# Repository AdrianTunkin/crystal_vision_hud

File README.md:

# CRYSTAL VISION HUD
### Head-Up Display (HUD) System for safe driving

#### Attention: This repository does not contain diagrams and drawings of projector optics. 
#### Also repository does not contain information regarding mechanical parts, including servos.

Crystal Vision is a portable Head-Up Display (HUD) system that projects an image on the windshield of your car. 
Both the driver and the passengers see it as a semi-transparent image that “levitates” over the hood of the car.

#### Copyright (C) 2015-2018, Crystal Vision Ltd.

https://user-images.githubusercontent.com/49099551/141296656-99a9382b-fc6b-408f-bb68-5c6743e9c2cb.mp4

## VISUAL CHARACTERISTICS

* Resolution: 854 x 480
* Perceived distance: 1.8-2.2 meters (depends on winshield geometry)
* Size: 17"
* Frequency: 60 Hz
* Color coverage:  ~70% sRGB
* Brightness: 1150 cd/m² (only for visible parts)
* Proprietary Remote Canvas technology

## TECHNICAL SPECIFICATIONS

* CPU: Allwinner H6 Quad-Core 64-bit Cortex-A53 @ 1.8GHz
* RAM: LPDDR3 2Gb @ 533Mhz
* ROM: 32Gb TF/MMC
* Power supply: DC 12V, 1.2A (max)
* Interfaces: IEEE 802.11 b/g/n (WiFi), Bluetooth 5.1, USB 2.0, OBDII
* Control OS: Android 9.0 Pie
* Dimensions: 83mm x 52mm x 30mm
* Weight: 115g

## TERMINOLOGY

* Projector - device for displaying projected images in windshield.
* Host phone — the phone on which the manager and client applications are installed.
* Manager - a gateway program through which client applications send graphic messages to the projector.
* Client application - an android application that, using the RemoteCanvas API, draws graphic messages on the projector. 

## DESCRIPTION

The CRYSTAL_HUD_MANAGER module is an android application that is installed on the host phone and acts as a gateway through which applications send messages to the projector.

The CRYSTAL_HUD_MANAGER function as a gateway includes:
* Controlling the concurrent access model of client applications to the projector
* Prioritize access for different applications
* Authorization of client applications.
* Work with three modes: asynchronous messages, synchronous messages, streaming. 

## WEB RESOURCES:

http://crystal-hud.tech Crystal Vision HUD information web site

https://github.com/AdrianTunkin/crystal_vision_hud - GitHub web site hosting the Hardware and Software sources

## LICENSE

### HARDWARE
The Hardware project is released under the Creative Commons Attribution-Share Alike 3.0 United States License.
You may reproduce it for both your own personal use, and for commercial use. 
You will have to provide a link to the original creator of the project http://crystal-hud.tech on any documentation or website.
You may also modify the files, but you must then release them as well under the same terms.
Credit can be attributed through a link to the creator website: http://crystal-hud.tech

### SOFTWARE
The software is released under GPL3.

### DOCUMENTATION
The documentation is released under the Creative Commons Attribution-Share Alike 3.0 United States License.

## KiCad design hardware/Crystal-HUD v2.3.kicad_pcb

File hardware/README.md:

# CRYSTAL VISION HUD
### Head-Up Display (HUD) System for safe driving

Crystal Vision is a portable Head-Up Display (HUD) system that projects an image on the windshield of your car. 
Both the driver and the passengers see it as a semi-transparent image that “levitates” over the hood of the car.

#### Copyright (C) 2015-2018, Crystal Vision Ltd.

Hardware directory contains hardware schematics, design sources, and revision changes designed in KiCad EDA software.

The Crystal Vision HUD electronic board is 6 layer PCB.

#### Technical specifications

* CPU: Allwinner H6 Quad-Core 64-bit Cortex-A53 @ 1.8GHz
* RAM: LPDDR3 2Gb @ 533Mhz
* ROM: 32Gb TF/MMC
* Power supply: DC 12V, 1.2A (max)
* Interfaces: IEEE 802.11 b/g/n (WiFi), Bluetooth 5.1, USB 2.0

### Hardware revision changes log:

#### Hardware revision 1.0

* initial release

#### Hardware revision 1.1

* 1. Adjusted white print of label
* 2. Added bypass near FET2
* 3. Added white print for the UART connector at the bottom of the board
* 4. Fixed white print of R106 and R116
* 5. R29 placed a bit further from C84

#### Hardware revision 2.0

* 1. Changed from eMMC 4GB 1.00mm pitch to eMMC  16GB 0.50mm pitch.
* 2. C212 and C213 were increased to 33pF and to 0402.
* 3. R66 value changed from NA(0R) to NA(22R)
* 4. RM15's package changed from RA1206_(4X0603)_4B8_22R to RA0805_(4X0402)_22R as component optimisation.
* 5. C119 and VR1 changed from PTH to SMT type in the KiCad settings. In reallity, C119 and VR1 did not change. 
* 6. PWRLED1 and CHGLED1 labels corrected in the white print.
* 7. WP_Enable1 jumper added to the SPI_Flash.
* 8. U4 changed from NA(H27UBG8T2BTR-BC(TSOP48)) to NA(MT29F64G08CBABA-WP(TSOP48)), i.e. when populated 8GB NAND instead of 4GB.

#### Hardware revision 2.1

* 1. eMMC KLMAG2GEND-B031(FBGA153)(16G) changed with new eMMC KLMAG1JETD-B041(FBGA153)(16G)

#### Hardware revision 2.2

* 1. Added R62(10k/0402) pull-down to the eMMC's data strobe line;
* 2. RM14, RA0805_(4X0402)_22R replaced by 4 resistors 22R/0402, i.e. R121-R124;
* 3. R73[NA(22R/0402)] was added to enable SPI0 software CS option to the UEXT via PH10, when the SPI_Flash is populated.
* 4. L9 was changed from 2.7nH/L0402 to NA(2.7nH/L0402), and C88 from 24pF to NA(24pF);
* 5. MIPI-DSI1 changed: MIPI-DSI1 connector's pinout completely changed for Raspberry-Pi compatability; added the resistors: R125 to R132;
* 6. In the DRC drill to drill clerance was set to 12mils and all related errors were corrected;
* 7. UEXT1 was changed from NA(HN2x5) to HN2x5;
* 8. All 3Ds were assigned;
* 9. It was added C94(NA/0402) to the eMMC's clock line just in case;
* 10. NAND and related components removed forever;
* 11. In the schematic all "/" signs were exchanged with "\";
* 12. Improvements around the placement of a number of resistors related to the PHY signals to reduce EMI emissions;
* 13. Added U4 EEPROM - AT24C16C-SSHM-T(SOIC-8_150mil) and also C39, 100nF/10V/10% to the UEXT's I2C to avoid conflict with the same EEPROM
* 14. R15[NA(22R/R0402)] added in serial to the eMMC's datastrobe signal to be able to disconnect when no HS400 mode or to add a serial filter to reduce EMI;
* 15. U2 and U3's packages improved;

#### Hardware revision 2.3

* 1. Added antenna ANT2(NA(U.FL-R-SMT-1)), R16(0R) and R17(NA/0R);
* 2. Removed FB1(FB0402/PZ1005U601-R45TF-1) and FB2(FB0402/PZ1005U601-R45TF-1) and placed R18(22R/0402) and R19(22R/0402) resistors instead.;
* 3. Adjusted the lengths of some eMMC wires;
* 4. C93 changed from 24pF to 24pF\50V/5%. C88 and C198 changed from NA/24pF to NA(24pF\50V/5%);
* 5. Changing 5.1 eMMC at 3.3V (up from 1.8V operation) for better reliability, PWR_PC1 jumper has to be set to position 1-2 for 3.3V operation.

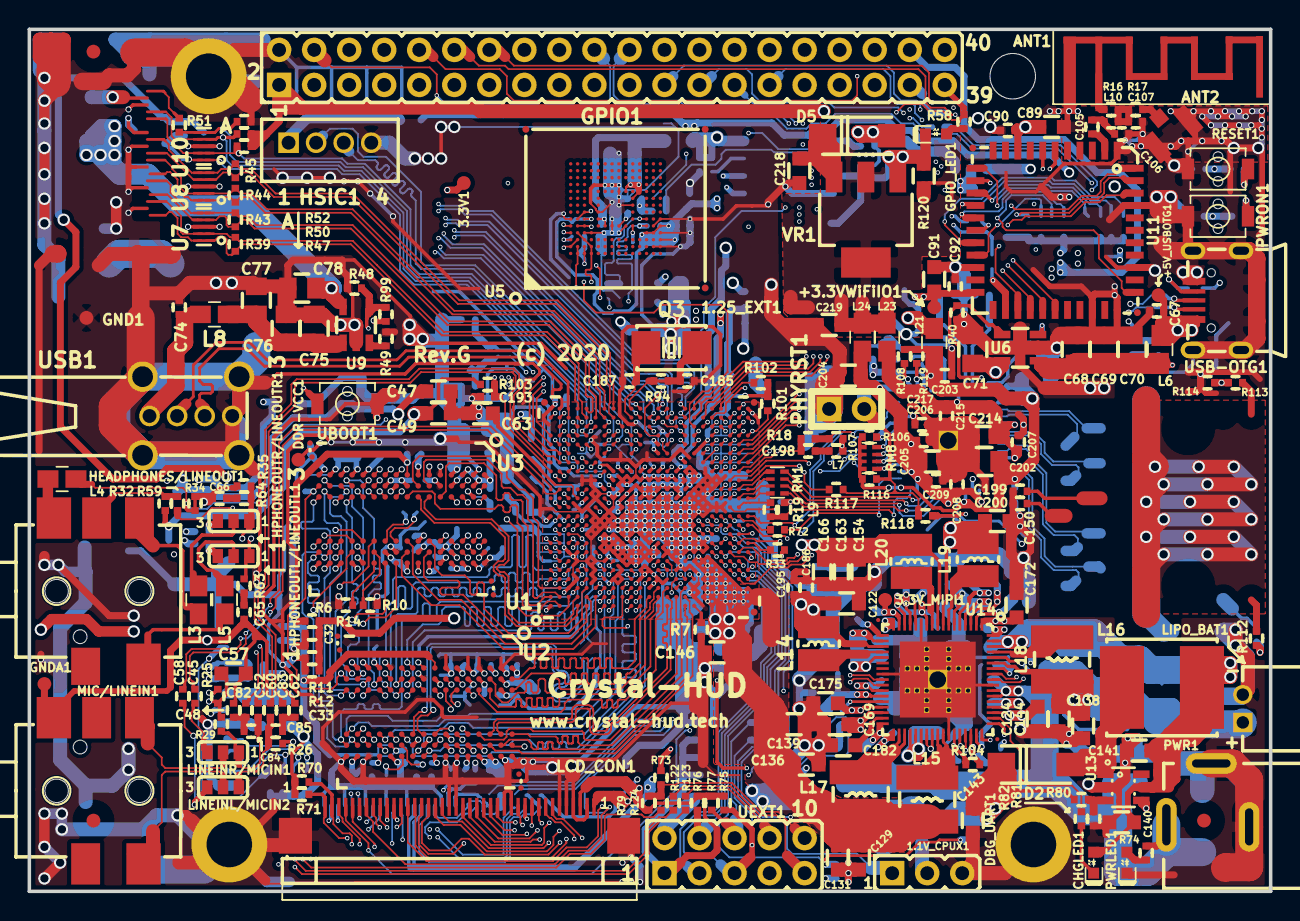
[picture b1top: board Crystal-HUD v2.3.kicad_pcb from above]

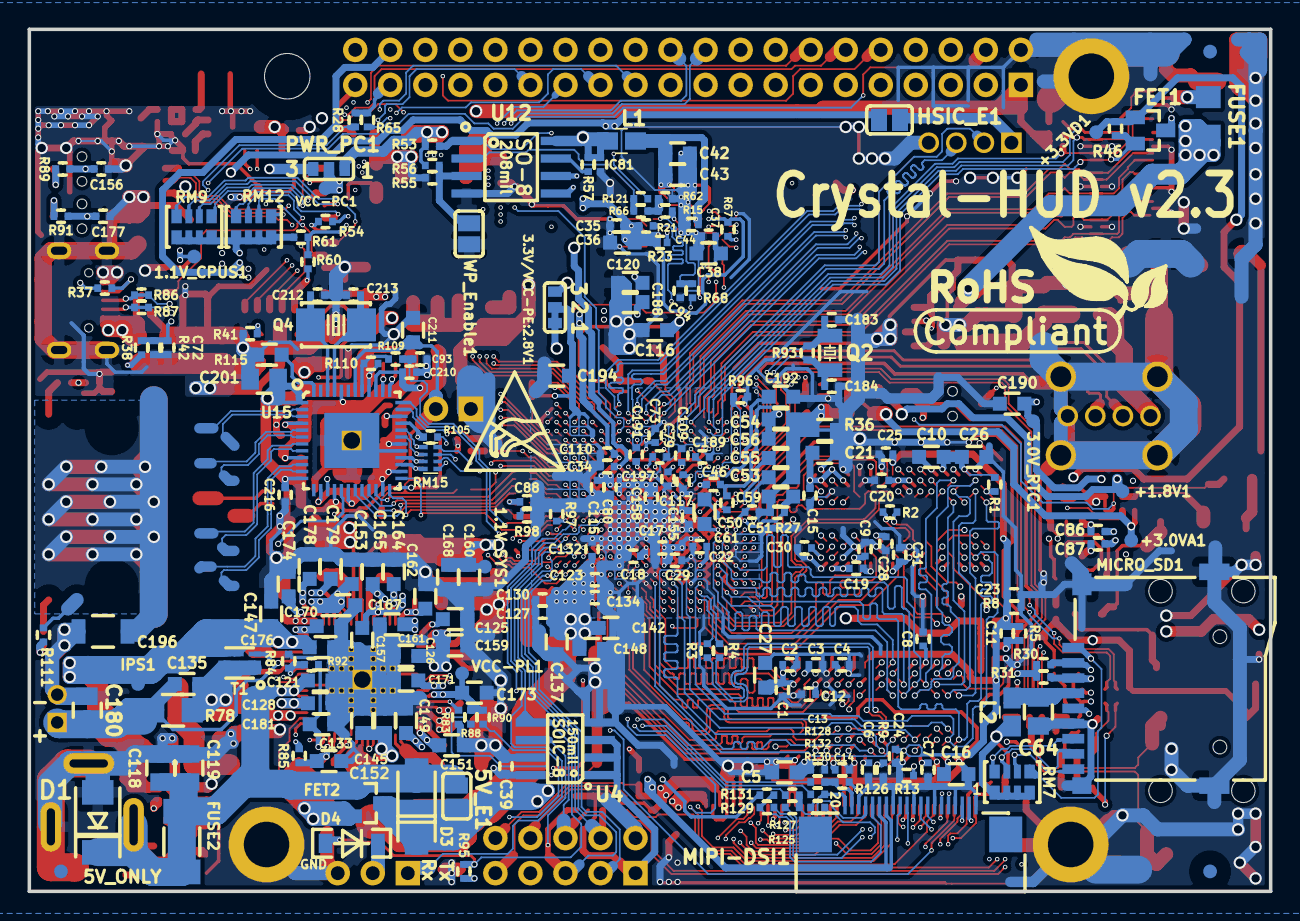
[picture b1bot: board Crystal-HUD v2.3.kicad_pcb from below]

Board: 6 copper layers, 90.0 x 62.5 mm, 445 parts (229 on the bottom side), 396 nets.

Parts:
1.1V_CPUS1, 1.1V_CPUX1, 1.1V_SYS1, 1.25_EXT1, 3.0V_RTC1, 3.3V1, 3.3V_MIPI1: TESTPAD; TP_SMD
3.3V/VCC-PE:2.8V1: Opened(2-3);Closed(1-2); SJ_2_SMALL_12_TIED
5V_E1: Opened; SJ
+1.8V1, +3.0VA1, +3.3VD1, +3.3VWiFiIO1, +5V_USBOTG1: TESTPAD; TP_SMD
ANT1: PCB_WIFI_ANT; BT_Antenna_Inverted_1ANT_2GND
ANT2: NA(U.FL-R-SMT-1); U.FL-R-SMT-1
C1, C2, C3, C4, C6, C7, C8, C9, C11, C12, C13, C14, C15, C17, C18, C19, C20, C22, C23, C24, C25, C32, C33, C34, C45, C46, C50, C51, C52, C58, C60, C65, C66, C67, C72, C73, C74, C79, C80, C82, C83, C86, C87, C109, C110, C115, C117, C123, C127, C130, C132, C134, C155, C156, C158, C177, C186, C189, C191, C195, C197, C199, C200, C203, C206, C207, C208, C209, C210, C215, C216, C217: 100nF\10V/10%; C_0402_5MIL_DWS
C5, C10, C16, C21, C47, C49, C53, C54, C57, C59, C63, C116, C121, C122, C124, C125, C126, C128, C129, C131, C133, C136, C138, C139, C140, C141, C143, C144, C145, C146, C147, C148, C149, C150, C151, C152, C153, C154, C157, C159, C161, C162, C164, C165, C166, C167, C168, C169, C170, C171, C172, C173, C175, C176, C178, C179, C188, C192, C194: 10uF\6.3V/20%; C_0603_5MIL_DWS
C26: 10uF/6.3V/20%; C_0603_5MIL_DWS
C27: 1uF/10V/10%; C_0603_5MIL_DWS
C28, C29, C30, C31, C39: 100nF/10V/10%; C_0402_5MIL_DWS
C35, C37, C44, C81, C90, C92: NA(100nF\10V/10%); C_0402_5MIL_DWS
C36, C38, C43: NA(2.2uF\6.3V/10%); C_0603_5MIL_DWS
C42: NA(22uF\6.3V/20%); C_0603_5MIL_DWS
C48, C62, C84, C85, C185, C187, C212, C213: 33pF\50V/5%; C_0402_5MIL_DWS
C55, C120, C135, C137, C142, C160, C163, C181, C182, C190, C211: 1uF\10V/10%; C_0603_5MIL_DWS
C56, C61: 2.2uF\6.3V/10%; C_0603_5MIL_DWS
C64, C68, C71, C75, C78, C118, C119, C180, C201, C202: 47uF\6.3V/20%; C_0805_5MIL_DWS
C69, C70, C76, C77: NA(47uF\6.3V/20%); C_0805_5MIL_DWS
C88, C198: NA(24pF\50V/5%); C_0402_5MIL_DWS
C89, C91, C174: NA(10uF\6.3V/20%); C_0603_5MIL_DWS
C93: 24pF\50V/5%; C_0402_5MIL_DWS
C94: NA; C_0402_5MIL_DWS
C105: NA(10pF\50V/5%); C_0402_5MIL_DWS
C106: NA(0.8pF\C0402); C_0402_5MIL_DWS
C107: NA(1.5pF\C0402); C_0402_5MIL_DWS
C183, C184: 22pF\50V/5%; C_0402_5MIL_DWS
C193: NA(1nF\50V/10%); C_0402_5MIL_DWS
C196: 1nF\2kV/10%/X7R; C_1206_5MIL_DWS_ISO
C204, C205, C214, C218, C219: 22uF\6.3V/20%; C_0603_5MIL_DWS
CHGLED1: LED\YELLOW/0603; LED_0603_KA
D1: SMBJ6.0A; DO214AA_1(K)-2(A)
D2, D3: 1N5822\SS34/SMA; SMA-KA
D4: 1N5819(S4SOD-123); SOD-123_1C-2A_KA
D5: 1N4007\SMA; SMA-KA
DBG_UART1: HN1x3
DDR-VCC1: TESTPAD; TP_SMD
FET1: BSS138(SOT23-3); SOT23
FET2: IRLML6402(SOT-23); SOT23
FID1, FID2, FID3, FID4, FID5, FID6: Fiducial1x3_transp
FUSE1: FSMD035; FUSE-1206
FUSE2: NA(5025); FUSE-5025
GND1: TESTPAD; TP_SMD
GNDA1: TESTPAD; TESTPAD_40-ROUND
GPIO1: NA(HN2x20); HN2x20
GPIO_LED1: LED\Red/0603; LED_0603_KA
HEADPHONES/LINEOUT1: SCJ325P00XG0B02G
HPHONEOUTL/LINEOUTL1: Soldered(1-2);Opened(2-3); SJ_2_SMALL
HPHONEOUTR/LINEOUTR1: Soldered(1-2);Opened(2-3); SJ_2_SMALL
HSIC1: NA(B4B-PH-K-S); B4B-PH-K-S
HSIC_E1: Opened; SJ
IPS1: TESTPAD; TP_SMD
L1: NA(FB0805\600R/2A); L_0805_5MIL_DWS
L2, L3, L4, L5, L6, L8, L21, L23, L24: FB0805\600R/2A; L_0805_5MIL_DWS
L7, L9: NA(2.7nH\L0402); L_0402_5MIL_DWS
L10: NA(3.3nH +-0.1nH LQP15MN3N3B02D); L_0402_5MIL_DWS
L14, L19, L20: SWPA3015S1R5NT(1.5uH\2.30A/DCR<0.1R/CD32); CD32
L15, L17, L18: SWPA4018S1R5NT(1.5uH\3.35A/DCR<0.1R/CD43); CD42(43)
L16: 2.2uH\3A/YS75/7x8; YS75_7X8MM
LCD_CON1: FPV-WZA21-40-LF
LINEINL/MICIN2: Opened(2-3);Soldered(1-2); SJ_2_SMALL
LINEINR/MICIN1: Opened(2-3);Soldered(1-2); SJ_2_SMALL
LIPO_BAT1: DW02R; LIPO_BAT-CON2DW02R
MIC/LINEIN1: SCJ325P00XG0B02G
MICRO_SD1: MICRO_SD(TFC-WPAPR-08); TFC-WPAPR-08
MIPI-DSI1: FPV-WZA21-20-LF
Mounting_hole1, Mounting_hole2, Mounting_hole3: Mounting_hole; Mounting_hole_3.3mm_with_5.5mm_pad
Mounting_hole4: Mounting_hole; Mounting_hole_3.3mm
PHYRST1: HN1x2(Opened); HN1x2_Jumper
PWR1: PWRJ-2mm(YDJ-1134)
PWRLED1: LED\Red/0603; LED_0603_KA
PWRON1: IT-1185AU2-160G-G-TR; IT1185AU2_V2
PWR_PC1: Opened(2-3);Soldered(1-2); SJ_2_SMALL
Q2: Q32.768kHz/12.5pF/2P/SMD1206; CM7V-T1A(Crystal_Package-1206_3.20x1.50x0.65mm)
Q3: Q24MHZ\20pF/20ppm/2P/5x3.2mm; HCX-4S_2Pins_5.0x3.2mm_TEST
Q4: Q25MHz\20pF/20ppm/2P/5x3.2mm; HCX-4S_2Pins_5.0x3.2mm_TEST
R1, R5, R8, R11, R12, R26, R29: 2k\1%; R_0402_5MIL_DWS
R2: 100R\1%; R_0402_5MIL_DWS
R3, R4, R18, R19, R33, R63, R64, R65, R72, R105, R109, R121, R122, R123, R124, R125, R126, R129, R130: 22R; R_0402_5MIL_DWS
R6, R55, R84, R96, R97, R98, R118, R127, R128, R131, R132: NA; R_0402_5MIL_DWS
R7, R9, R10: 243R\1%; R_0402_5MIL_DWS
R13, R14: NA(243R\1%); R_0402_5MIL_DWS
R15, R54, R66, R68, R73: NA(22R); R_0402_5MIL_DWS
R16: 0R; R_0402_5MIL_DWS
R17, R60: NA(0R); R_0402_5MIL_DWS
R21, R23, R48, R53, R56, R57, R61, R62, R67, R104: NA(10k); R_0402_5MIL_DWS
R25: 470R; R_0402_5MIL_DWS
R27: 200k\1%; R_0402_5MIL_DWS
R28: NA(1k); R_0402_5MIL_DWS
R30, R35, R103, R116: 100k; R_0402_5MIL_DWS
R31, R37, R40, R42, R52, R76, R79, R83, R85, R95, R99, R106, R119: 10k; R_0402_5MIL_DWS
R32: NA(1M); R_0402_5MIL_DWS
R34, R86, R87, R94: 0R(Board_Mounted); R_0402_5MIL_0R(Board_Mounted)
R36: 0R(Board_Mounted); R_0603_5MIL_0R(Board_Mounted)
R38, R51: 4.7k; R_0402_5MIL_DWS
R39, R43, R44, R45: NA(510R); R_0402_5MIL_DWS
R41: 13k\1%; R_0402_5MIL_DWS
R46: 27k; R_0402_5MIL_DWS
R47, R50, R70, R71, R74, R75, R77, R82, R88, R90: 2.2k; R_0402_5MIL_DWS
R49: 3.92k\1%; R_0402_5MIL_DWS
R58, R89, R91, R92, R107, R108, R110, R111, R112, R113, R114, R117: 1k; R_0402_5MIL_DWS
R59: 47k; R_0402_5MIL_DWS
R78: 0.01R\1%/1206; R_1206_5MIL_DWS
R80: 8.25k\1%; R_0402_5MIL_DWS
R81: 1.1k\1%; R_0402_5MIL_DWS
R93: 10M; R_0402_5MIL_DWS
R101, R102: NA(2.2k); R_0402_5MIL_DWS
R115: 12.1k\1%; R_0603_5MIL_DWS
R120: 120R; R_0603_5MIL_DWS
RESET1: IT-1185AU2-160G-G-TR; IT1185AU2_V2
RM1, RM15: RA0805_(4X0402)_22R; RA0805_(4X0402)_xx_BIGGEROUTPADS
RM7: RA1206_(4x0603)_4B8_100k; RA1206_(4X0603)_4B8_xx
RM8: RA0805_(4X0402)_4.7k; RA0805_(4X0402)_xx_BIGGEROUTPADS
RM9, RM12: NA(RA1206_(4x0603)_4B8_100k); RA1206_(4X0603)_4B8_xx
Sign-Antistatic: LOGO_ANTISTATIC_1
Sign-RoHS: LOGO_ROHS_1
T1: WPM1481-6\TR(DFN2X2-6L); DFN2x2-6L
U1: AllWinner-A64(FBGA396); FBGA396
U2, U3: K4B4G1646Q-HYK0(FBGA-96_256Mx16_DDR3-1600_11-11-1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; FBGA96(HYNIX_SAMSUNG_512MX16_DDR3)
U4: AT24C16C-SSHM-T(SOIC-8_150mil); SOIC-8_150mil
U5: NA(KLMAG2GEND-B031(FBGA153)); FBGA153_Pitch-0.5mm_Ball-0.25mm_Dimensions-11.50x13.00x0.80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
U6, U9: SY6280AAC(SOT23-5); SOT-23-5
U7, U8, U10: NA(RCLAMP0524P(SLP2510P8)); SLP2510P8_TEST
U11: NA(RTL8723BS(ComboModule)); RL-SM02BD(RTL8723BS)
U12: NA(W25Q128FVSIG); SO-8_208mil
U13: MT3608(SOT23-6); SOT23-6
U14: AXP803(QFN68_8x8mm); QFN68
U15: KSZ9031RNXCC(QFN48_1DRILL(PADPITCH-0.5MM)); QFN48_1DRILL(PADPITCH-0.5MM)
UBOOT1: IT-1185AU2-160G-G-TR; IT1185AU2_V2
UEXT1: HN2x5
USB1: USB_A_VERTICAL; USB_A_VERTICAL_PTH
USB-OTG1: MICRO_USB\MISB-SWMM-5B_LF; USB-MICRO_MISB-SWMM-5B_LF
VCC-PC1: TESTPAD; TP_SMD
VCC-PL1: TESTPAD; TP_SMD
VR1: AMS1117(ADJ); SOT223
WP_Enable1: Opened; SJ

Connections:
1.1V_CPUS: 1.1V_CPUS1.1, C117.2, C120.2, C179.2, U1.H15, U14.5
1.1V_CPUX: 1.1V_CPUX1.1, C123.2, C127.2, C129.2, C130.2, C131.2, C132.2, C134.2, C136.2, C137.2, C139.2, C142.2, C146.2, C148.2, L15.2, L17.2, U1.AA1, U1.AA3, U1.AB2, U1.AC1, U1.AC2, U1.U6, U1.V2, U1.V3, U1.V4, U1.V5, U1.V6, U1.W1, U1.W3, U1.W4, U1.W5, U1.Y2, U1.Y3, U1.Y4
1.1V_SYS: 1.1V_SYS1.1, C154.2, C155.2, C158.2, C160.2, C163.2, C166.2, C168.2, L20.2, U1.J12, U1.J13, U1.K14, U1.L13, U1.L14, U1.M13, U1.M14, U1.N14, U1.P14, U1.R13, U1.R14, U1.T15, U14.9
1.2V_HSIC: C178.2, C197.1, HSIC_E1.1, U1.K16, U14.3
3.0V_RTC: 3.0V_RTC1.1, C152.1, C189.2, C190.2, R85.2, R104.1, U1.H16, U14.49
+1.5V: C1.1, C2.1, C3.1, C4.1, C5.1, C6.1, C7.1, C8.1, C9.1, C10.1, C11.1, C12.1, C13.1, C14.1, C15.1, C16.1, C17.1, C18.1, C19.1, C20.1, C21.1, C26.1, C27.1, C28.1, C29.1, C30.1, C31.1, C32.2, C150.2, DDR-VCC1.1, L19.2, R1.2, R5.2, R11.2, U1.G7, U1.G8, U1.G9, U1.J8, U1.K6, U1.K7, U1.L6, U1.L7, U1.L8, U1.N7, U1.N8, U2.A1, U2.A8, U2.B2, U2.C1, U2.C9, U2.D2, U2.D9, U2.E9, U2.F1, U2.G7, U2.H2, U2.H9, U2.K2, U2.K8, U2.N1, U2.N9, U2.R1, U2.R9, U3.A1, U3.A8, U3.B2, U3.C1, U3.C9, U3.D2, U3.D9, U3.E9, U3.F1, U3.G7, U3.H2, U3.H9, U3.K2, U3.K8, U3.N1, U3.N9, U3.R1, U3.R9, U14.8
+1V8: +1.8V1.1, C47.2, C50.2, C170.2, PWR_PC1.3, U1.E13, U14.68
+3.0VA: +3.0VA1.1, C46.1, C49.1, C175.1, C191.2, R32.2, R103.1, U1.G14, U1.N16, U14.31
+3.3VD: +3.3VD1.1, C79.2, C161.2, FET1.1, R46.1, U1.M16, U14.17
+3.3VWiFiIO: +3.3VWiFiIO1.1, C91.2, C92.2, C110.2, C165.2, R61.2, RM9.1.1, RM9.2.1, RM9.3.1, RM9.4.1, RM12.1.1, RM12.2.1, RM12.3.1, RM12.4.1, U1.T17, U11.22, U14.13
+3V3: 3.3V1.1, 3.3V/VCC-PE:2.8V1.3, C39.1, C73.2, C80.1, C81.2, C89.2, C90.2, C115.2, C116.2, C122.2, C186.2, C195.2, D5.2, GPIO1.3, L1.1, L2.1, L14.2, L21.2, LCD_CON1.3, PWR_PC1.1, R30.2, R31.2, R37.2, R53.2, R56.2, R57.2, R70.2, R71.2, R75.1, R76.1, R77.1, R79.1, R95.2, R99.1, RM7.1.1, RM7.2.1, RM7.3.1, RM7.4.1, U1.L16, U1.N18, U1.N19, U1.T14, U1.U15, U1.U16, U4.1, U4.2, U4.3, U4.8, U11.9, U12.8, U13.4, U14.20, UEXT1.1
+5V: 5V_E1.2, C71.1, C78.1, D3.1, FET2.3, FUSE1.1, GPIO1.1, LCD_CON1.1, R47.1, R50.1, U6.5, U9.5
+5V_EXT: 5V_E1.1, C118.2, C119.2, C121.1, D1.1, D3.2, FET2.1, FUSE2.1, FUSE2.2, PWR1.+, R74.1, U14.57, U14.58
+5V_USBOTG: +5V_USBOTG1.1, C67.1, C124.1, L6.2, U14.54, USB-OTG1.1
/NAND Flash , eMMC, T-Card and Audio/HP-DET: R59.2, U1.D11
/NAND Flash , eMMC, T-Card and Audio/HPOUTFB: L4.1, R34.2, U1.C10
/NAND Flash , eMMC, T-Card and Audio/HPOUTL: HPHONEOUTL/LINEOUTL1.1, R63.2, U1.C13
/NAND Flash , eMMC, T-Card and Audio/HPOUTR: HPHONEOUTR/LINEOUTR1.1, R35.2, R64.2, U1.C12
/NAND Flash , eMMC, T-Card and Audio/LINEINL: C58.2, U1.B14
/NAND Flash , eMMC, T-Card and Audio/LINEINR: C45.2, U1.A14
/NAND Flash , eMMC, T-Card and Audio/LINEOUTL: C87.1, U1.D16
/NAND Flash , eMMC, T-Card and Audio/LINEOUTR: C86.1, U1.C16
/NAND Flash , eMMC, T-Card and Audio/MBIAS: R25.2, U1.E14
/NAND Flash , eMMC, T-Card and Audio/MICIN1N: C82.2, U1.B16
/NAND Flash , eMMC, T-Card and Audio/MICIN1P: C52.2, U1.B15
/NAND Flash , eMMC, T-Card and Audio/MICIN2N: C83.2, U1.A17
/NAND Flash , eMMC, T-Card and Audio/MICIN2P: C60.2, U1.B17
/NAND Flash , eMMC, T-Card and Audio/NAND0-ALE\SDC2-DS: R15.2, R62.1, R66.2, U1.K18
/NAND Flash , eMMC, T-Card and Audio/NAND0-DQ0\SDC2-D0: R67.1, U1.M21, U5.A3
/NAND Flash , eMMC, T-Card and Audio/NAND0-DQ1\SDC2-D1: U1.L19, U5.A4
/NAND Flash , eMMC, T-Card and Audio/NAND0-DQ2\SDC2-D2: U1.K20, U5.A5
/NAND Flash , eMMC, T-Card and Audio/NAND0-DQ3\SDC2-D3: U1.H20, U5.B2
/NAND Flash , eMMC, T-Card and Audio/NAND0-DQ4\SDC2-D4: U1.P18, U5.B3
/NAND Flash , eMMC, T-Card and Audio/NAND0-DQ5\SDC2-D5: U1.L20, U5.B4
/NAND Flash , eMMC, T-Card and Audio/NAND0-DQ6\SDC2-D6: U1.J21, U5.B5
/NAND Flash , eMMC, T-Card and Audio/NAND0-DQ7\SDC2-D7: U1.R21, U5.B6
/NAND Flash , eMMC, T-Card and Audio/NAND0-DQS\SDC2-RST: R23.1, U1.N20, U5.K5
/NAND Flash , eMMC, T-Card and Audio/NAND0-RB0\SDC2-CMD: R21.1, U1.K19, U5.M5
/NAND Flash , eMMC, T-Card and Audio/NAND0-RE\SDC2-CLK: R68.2, U1.G20
/NAND Flash , eMMC, T-Card and Audio/SDC0-CLK: R33.2, U1.AC8
/NAND Flash , eMMC, T-Card and Audio/SDC0-CMD: MICRO_SD1.3, R31.1, U1.W9
/NAND Flash , eMMC, T-Card and Audio/SDC0-D0: MICRO_SD1.7, RM7.1.2, U1.W13
/NAND Flash , eMMC, T-Card and Audio/SDC0-D1: MICRO_SD1.8, RM7.2.2, U1.AB10
/NAND Flash , eMMC, T-Card and Audio/SDC0-D2: MICRO_SD1.1, RM7.4.2, U1.AB9
/NAND Flash , eMMC, T-Card and Audio/SDC0-D3: MICRO_SD1.2, R30.1, U1.AB6
/NAND Flash , eMMC, T-Card and Audio/SDC0-DET#: MICRO_SD1.9, RM7.3.2, U1.AB8
/NAND Flash , eMMC, T-Card and Audio/eMMC_CLK: C94.1, R68.1, U5.M6
/Power Supply, Extensions and MiPi-DSI/1.8V_DVDD-CSI: C172.2, GPIO1.36, U14.1
/Power Supply, Extensions and MiPi-DSI/2.8V_AVDD-CSI: C164.2, GPIO1.38, U14.14
/Power Supply, Extensions and MiPi-DSI/3.3V_MIPI: 3.3V_MIPI1.1, C162.2, MIPI-DSI1.14, MIPI-DSI1.15, U14.16
/Power Supply, Extensions and MiPi-DSI/DC5SET: R84.2, R92.1, U14.62
/Power Supply, Extensions and MiPi-DSI/DSI-CKN: MIPI-DSI1.5, U1.P23
/Power Supply, Extensions and MiPi-DSI/DSI-CKP: MIPI-DSI1.6, U1.N23
/Power Supply, Extensions and MiPi-DSI/DSI-D0N: MIPI-DSI1.8, U1.T23
/Power Supply, Extensions and MiPi-DSI/DSI-D0P: MIPI-DSI1.9, U1.T22
/Power Supply, Extensions and MiPi-DSI/DSI-D1N: MIPI-DSI1.2, U1.R22
/Power Supply, Extensions and MiPi-DSI/DSI-D1P: MIPI-DSI1.3, U1.P22
/Power Supply, Extensions and MiPi-DSI/DSI-D2N: R126.2, U1.N22
/Power Supply, Extensions and MiPi-DSI/DSI-D2P: R130.1, U1.M22
/Power Supply, Extensions and MiPi-DSI/DSI-D3N: R129.1, U1.L22
/Power Supply, Extensions and MiPi-DSI/DSI-D3P: R125.2, U1.L23
/Power Supply, Extensions and MiPi-DSI/MIPI-DSI-BKL: R132.1, U1.W8
/Power Supply, Extensions and MiPi-DSI/MIPI-DSI-EN: R128.2, U1.Y6
/Power Supply, Extensions and MiPi-DSI/MIPI-DSI-RST: R127.2, U1.AA6
/Power Supply, Extensions and MiPi-DSI/PB0: GPIO1.10, U1.V9
/Power Supply, Extensions and MiPi-DSI/PB1: GPIO1.12, U1.AB7
/Power Supply, Extensions and MiPi-DSI/PB2: GPIO1.14, U1.W10
/Power Supply, Extensions and MiPi-DSI/PB3: GPIO1.16, U1.AA7
/Power Supply, Extensions and MiPi-DSI/PB4: GPIO1.18, U1.W7
/Power Supply, Extensions and MiPi-DSI/PE0: GPIO1.5, U1.AA18
/Power Supply, Extensions and MiPi-DSI/PE1: GPIO1.7, U1.AB23
/Power Supply, Extensions and MiPi-DSI/PE2: GPIO1.9, U1.AA22
/Power Supply, Extensions and MiPi-DSI/PE3: GPIO1.11, U1.AA21
/Power Supply, Extensions and MiPi-DSI/PE4: GPIO1.13, U1.AA19
/Power Supply, Extensions and MiPi-DSI/PE5: GPIO1.15, U1.W17
/Power Supply, Extensions and MiPi-DSI/PE6: GPIO1.17, U1.W20
/Power Supply, Extensions and MiPi-DSI/PE7: GPIO1.19, U1.Y19
/Power Supply, Extensions and MiPi-DSI/PE8: GPIO1.21, U1.AC22
/Power Supply, Extensions and MiPi-DSI/PE9: GPIO1.23, U1.Y17
/Power Supply, Extensions and MiPi-DSI/PE10: GPIO1.25, U1.AB22
/Power Supply, Extensions and MiPi-DSI/PE11: GPIO1.27, U1.W21
/Power Supply, Extensions and MiPi-DSI/PE12: GPIO1.29, U1.AB20
/Power Supply, Extensions and MiPi-DSI/PE13: GPIO1.31, U1.Y22
/Power Supply, Extensions and MiPi-DSI/PE14: GPIO1.33, R101.1, U1.AC20
/Power Supply, Extensions and MiPi-DSI/PE15: GPIO1.35, R102.1, U1.Y23
/Power Supply, Extensions and MiPi-DSI/PE16: R65.2, U1.AB21
/Power Supply, Extensions and MiPi-DSI/PE16\POWERON: GPIO1.37, R28.1, R65.1
/Power Supply, Extensions and MiPi-DSI/PE17\GPIO_LED: GPIO1.39, R58.1, U1.W22
/Power Supply, Extensions and MiPi-DSI/UEXT-CLK: R122.1, UEXT1.9
/Power Supply, Extensions and MiPi-DSI/UEXT-CS: R73.2, R79.2, R124.2, UEXT1.10
/Power Supply, Extensions and MiPi-DSI/UEXT-MISO: R121.1, UEXT1.7
/Power Supply, Extensions and MiPi-DSI/UEXT-MOSI: R123.2, UEXT1.8
/S0SA0: U1.P5, U2.N3, U3.N3
/S0SA1: U1.R4, U2.P7, U3.P7
/S0SA2: U1.N5, U2.P3, U3.P3
/S0SA3: U1.N6, U2.N2, U3.N2
/S0SA4: U1.P6, U2.P8, U3.P8
/S0SA5: U1.G4, U2.P2, U3.P2
/S0SA6: U1.F3, U2.R8, U3.R8
/S0SA7: U1.E4, U2.R2, U3.R2
/S0SA8: U1.D3, U2.T8, U3.T8
/S0SA9: U1.C4, U2.R3, U3.R3
/S0SA10: U1.M4, U2.L7, U3.L7
/S0SA11: U1.U4, U2.R7, U3.R7
/S0SA12: U1.K5, U2.N7, U3.N7
/S0SA13: U1.E8, U2.T3, U3.T3
/S0SA14: U1.K4, U2.T7, U3.T7
/S0SA15: U1.T4, U2.M7, U3.M7
/S0SBA0: U1.D8, U2.M2, U3.M2
/S0SBA1: U1.R3, U2.N8, U3.N8
/S0SBA2: U1.C6, U2.M3, U3.M3
/S0SCAS: U1.C9, U2.K3, U3.K3
/S0SCKE0: U1.J3, U2.K9, U3.K9
/S0SCKE1: U1.H6, U2.J9, U3.J9
/S0SCK_N: R2.1, R4.1, U2.K7, U3.K7
/S0SCK_P: R2.2, R3.1, U2.J7, U3.J7
/S0SCS0: U1.E5, U2.L2, U3.L2
/S0SCS1: U1.H5, U2.L1, U3.L1
/S0SDQ0: U1.L3, U2.F7
/S0SDQ1: U1.G1, U2.G2
/S0SDQ2: U1.H3, U2.F2
/S0SDQ3: U1.K1, U2.H7
/S0SDQ4: U1.H2, U2.E3
/S0SDQ5: U1.H1, U2.H3
/S0SDQ6: U1.L1, U2.H8
/S0SDQ7: U1.L2, U2.F8
/S0SDQ8: U1.T3, U2.A7
/S0SDQ9: U1.T2, U2.C8
/S0SDQ10: U1.T1, U2.B8
/S0SDQ11: U1.R2, U2.D7
/S0SDQ12: U1.N3, U2.A3
/S0SDQ13: U1.N2, U2.C2
/S0SDQ14: U1.N1, U2.C3
/S0SDQ15: U1.M2, U2.A2
/S0SDQ16: U1.E3, U3.F7
/S0SDQ17: U1.F2, U3.H8
/S0SDQ18: U1.E2, U3.H7
/S0SDQ19: U1.E1, U3.F8
/S0SDQ20: U1.B1, U3.H3
/S0SDQ21: U1.B2, U3.F2
/S0SDQ22: U1.A2, U3.E3
/S0SDQ23: U1.B3, U3.G2
/S0SDQ24: U1.C5, U3.A7
/S0SDQ25: U1.B4, U3.C8
/S0SDQ26: U1.A4, U3.D7
/S0SDQ27: U1.A5, U3.B8
/S0SDQ28: U1.A7, U3.A3
/S0SDQ29: U1.A8, U3.C3
/S0SDQ30: U1.B8, U3.A2
/S0SDQ31: U1.B9, U3.C2
/S0SDQM0: U1.J2, U2.E7
/S0SDQM1: U1.P3, U2.D3
/S0SDQM2: U1.C2, U3.E7
/S0SDQM3: U1.B7, U3.D3
/S0SDQS0_N: U1.K2, U2.G3
/S0SDQS0_P: U1.K3, U2.F3
/S0SDQS1_N: U1.P2, U2.B7
/S0SDQS1_P: U1.P1, U2.C7
/S0SDQS2_N: U1.D1, U3.G3
/S0SDQS2_P: U1.D2, U3.F3
/S0SDQS3_N: U1.B5, U3.B7
/S0SDQS3_P: U1.B6, U3.C7
/S0SODT0: U1.D5, U2.K1, U3.K1
/S0SODT1: U1.E7, U2.J1, U3.J1
/S0SRAS: U1.F7, U2.J3, U3.J3
/S0SRST: R1.1, U1.D10, U2.T2, U3.T2
/S0SVREF: C22.2, C32.1, C33.2, R6.2, R11.1, R12.2, U1.G5
/S0SWE: U1.C8, U2.L3, U3.L3
/USB&HDMI,WiFi&BT,Ethernet,LCD/1.25_EXT: 1.25_EXT1.1, C219.1, L23.2, L24.2, R120.1, VR1.2
/USB&HDMI,WiFi&BT,Ethernet,LCD/AP-WAKE-BT: U1.B20, U11.6
/USB&HDMI,WiFi&BT,Ethernet,LCD/BT-PCM-CLK: U1.AB18, U11.26
/USB&HDMI,WiFi&BT,Ethernet,LCD/BT-PCM-DIN: U1.AC19, U11.27
/USB&HDMI,WiFi&BT,Ethernet,LCD/BT-PCM-DOUT: U1.U22, U11.25
/USB&HDMI,WiFi&BT,Ethernet,LCD/BT-PCM-SYNC: U1.AB19, U11.28
/USB&HDMI,WiFi&BT,Ethernet,LCD/BT-RST-N: RM12.2.2, U1.A20, U11.34
/USB&HDMI,WiFi&BT,Ethernet,LCD/BT-UART-CTS: U1.AC17, U11.44
/USB&HDMI,WiFi&BT,Ethernet,LCD/BT-UART-RX: RM12.4.2, U1.AB17, U11.43
/USB&HDMI,WiFi&BT,Ethernet,LCD/BT-UART-TX: U1.U23, U11.42
/USB&HDMI,WiFi&BT,Ethernet,LCD/BT-WAKE-AP: U1.D19, U11.7
/USB&HDMI,WiFi&BT,Ethernet,LCD/EPHY-RST#: R117.2, U1.Y14
/USB&HDMI,WiFi&BT,Ethernet,LCD/GCLKIN\LCD_VSYNC: C93.2, LCD_CON1.30, R109.1, U1.AC11
/USB&HDMI,WiFi&BT,Ethernet,LCD/GMDC\LCD-PWM: LCD_CON1.36, U1.Y13, U15.36
/USB&HDMI,WiFi&BT,Ethernet,LCD/GMDIO\LCD_PWR: LCD_CON1.35, R108.1, U1.AC10, U15.37
/USB&HDMI,WiFi&BT,Ethernet,LCD/GRXCK\LCD_D18: C198.1, LCD_CON1.7, R18.1, U1.AC16
/USB&HDMI,WiFi&BT,Ethernet,LCD/GRXCTL\LCD_D19: LCD_CON1.8, R105.1, U1.AB16
/USB&HDMI,WiFi&BT,Ethernet,LCD/GRXD0\LCD_D15: LCD_CON1.20, RM15.1.2, U1.Y16
/USB&HDMI,WiFi&BT,Ethernet,LCD/GRXD1\LCD_D14: LCD_CON1.19, RM15.2.2, U1.W16
/USB&HDMI,WiFi&BT,Ethernet,LCD/GRXD2\LCD_D13: LCD_CON1.18, RM15.3.2, U1.AA13
/USB&HDMI,WiFi&BT,Ethernet,LCD/GRXD3\LCD_D12: LCD_CON1.17, RM15.4.2, U1.V17
/USB&HDMI,WiFi&BT,Ethernet,LCD/GTXCK\LCD_DE: L9.2, LCD_CON1.32, R19.2, U15.24
/USB&HDMI,WiFi&BT,Ethernet,LCD/GTXCTL\LCD_HSYNC: LCD_CON1.29, R72.2, U15.25
/USB&HDMI,WiFi&BT,Ethernet,LCD/GTXD0\LCD_CLK: LCD_CON1.31, RM1.2.1, U15.19
/USB&HDMI,WiFi&BT,Ethernet,LCD/GTXD1\LCD_D23: LCD_CON1.12, RM1.1.1, U15.20
/USB&HDMI,WiFi&BT,Ethernet,LCD/GTXD2\LCD_D22: LCD_CON1.11, RM1.3.1, U15.21
/USB&HDMI,WiFi&BT,Ethernet,LCD/GTXD3\LCD_D21: LCD_CON1.10, RM1.4.1, U15.22
/USB&HDMI,WiFi&BT,Ethernet,LCD/HCEC: FET1.2, R46.2, U1.F21, U10.1, U10.10
/USB&HDMI,WiFi&BT,Ethernet,LCD/HHPD: R51.1, R52.1, U1.E21, U10.5, U10.6
/USB&HDMI,WiFi&BT,Ethernet,LCD/HSCL: R47.2, U1.G21, U10.2, U10.9
/USB&HDMI,WiFi&BT,Ethernet,LCD/HSDA: R50.2, U1.E20, U10.4, U10.7
/USB&HDMI,WiFi&BT,Ethernet,LCD/HTX0N: R44.1, U1.G23, U8.2, U8.9
/USB&HDMI,WiFi&BT,Ethernet,LCD/HTX0P: R44.2, U1.G22, U8.1, U8.10
/USB&HDMI,WiFi&BT,Ethernet,LCD/HTX1N: R43.2, U1.F22, U7.5, U7.6
/USB&HDMI,WiFi&BT,Ethernet,LCD/HTX1P: R43.1, U1.E23, U7.4, U7.7
/USB&HDMI,WiFi&BT,Ethernet,LCD/HTX2N: R39.1, U1.E22, U7.2, U7.9
/USB&HDMI,WiFi&BT,Ethernet,LCD/HTX2P: R39.2, U1.D23, U7.1, U7.10
/USB&HDMI,WiFi&BT,Ethernet,LCD/HTXCN: R45.2, U1.H23, U8.5, U8.6
/USB&HDMI,WiFi&BT,Ethernet,LCD/HTXCP: R45.1, U1.H22, U8.4, U8.7
/USB&HDMI,WiFi&BT,Ethernet,LCD/LCD_D2: LCD_CON1.23, U1.AA20
/USB&HDMI,WiFi&BT,Ethernet,LCD/LCD_D3: LCD_CON1.24, U1.AA17
/USB&HDMI,WiFi&BT,Ethernet,LCD/LCD_D4: LCD_CON1.25, U1.W19
/USB&HDMI,WiFi&BT,Ethernet,LCD/LCD_D5: LCD_CON1.26, U1.AA14
/USB&HDMI,WiFi&BT,Ethernet,LCD/LCD_D6: LCD_CON1.27, U1.V18
/USB&HDMI,WiFi&BT,Ethernet,LCD/LCD_D7: LCD_CON1.28, U1.AA15
/USB&HDMI,WiFi&BT,Ethernet,LCD/LCD_D10: LCD_CON1.15, U1.Y11
/USB&HDMI,WiFi&BT,Ethernet,LCD/LCD_D11: LCD_CON1.16, U1.AA16
/USB&HDMI,WiFi&BT,Ethernet,LCD/LCD_D20: LCD_CON1.9, U1.AB15
/USB&HDMI,WiFi&BT,Ethernet,LCD/PH7\CTP-INT: LCD_CON1.37, U1.AC5
/USB&HDMI,WiFi&BT,Ethernet,LCD/PH8\CTP-RST: LCD_CON1.38, U1.Y10
/USB&HDMI,WiFi&BT,Ethernet,LCD/USB0-ID: R37.1, U1.AA8, USB-OTG1.4
/USB&HDMI,WiFi&BT,Ethernet,LCD/USB0-VBUSDET: C72.2, R38.1, R42.2, U1.AB4
/USB&HDMI,WiFi&BT,Ethernet,LCD/USB1-DM: U1.C22, USB1.2
/USB&HDMI,WiFi&BT,Ethernet,LCD/USB1-DP: U1.B23, USB1.3
/USB&HDMI,WiFi&BT,Ethernet,LCD/VDD33: C201.1, C202.1, C203.2, C216.2, C217.2, L21.1, R106.1, R108.2, R110.1, R111.1, R116.2, R119.2, RM8.1.1, RM8.2.1, RM8.3.1, RM8.4.1, U15.1, U15.12, U15.16, U15.34, U15.40
/USB&HDMI,WiFi&BT,Ethernet,LCD/WL-PMU-EN: RM9.4.2, U1.A19, U11.12
/USB&HDMI,WiFi&BT,Ethernet,LCD/WL-SDIO-CLK: R54.2, U1.V21
/USB&HDMI,WiFi&BT,Ethernet,LCD/WL-SDIO-CMD: RM12.1.2, U1.U20, U11.16
/USB&HDMI,WiFi&BT,Ethernet,LCD/WL-SDIO-D0: RM9.1.2, U1.U19, U11.18
/USB&HDMI,WiFi&BT,Ethernet,LCD/WL-SDIO-D1: RM12.3.2, U1.V22, U11.19
/USB&HDMI,WiFi&BT,Ethernet,LCD/WL-SDIO-D2: RM9.3.2, U1.Y21, U11.14
/USB&HDMI,WiFi&BT,Ethernet,LCD/WL-SDIO-D3: RM9.2.2, U1.W23, U11.15
/USB&HDMI,WiFi&BT,Ethernet,LCD/WL-WAKE-AP: U1.E19, U11.13
/VREF0_DDR3: C11.2, C23.1, C24.1, C25.1, R5.1, R6.1, R8.2, U2.H1, U2.M8, U3.H1, U3.M8
AP-CK32KO: R60.2, R61.1, U1.B18
AP-NMI#: R85.1, U1.G18, U14.61
AP-RESET#: C156.2, GPIO1.4, R89.2, R104.2, R118.2, U1.E17, U14.46
GND: ANT1.2, ANT2.2, C1.2, C2.2, C3.2, C4.2, C5.2, C6.2, C7.2, C8.2, C9.2, C10.2, C12.2, C13.2, C14.2, C15.2, C16.2, C17.2, C18.2, C19.2, C20.2, C21.2, C22.1, C23.2, C24.2, C25.2, C26.2, C27.2, C28.2, C29.2, C30.2, C31.2, C33.1, C34.1, C35.1, C36.1, C37.1, C38.1, C39.2, C42.2, C43.2, C44.2, C64.2, C67.2, C68.1, C69.1, C70.1, C71.2, C72.1, C73.1, C74.2, C75.1, C76.1, C77.1, C78.2, C79.1, C80.2, C81.1, C88.1, C89.1, C90.1, C91.1, C92.1, C93.1, C94.2, C106.1, C107.1, C109.2, C110.1, C115.1, C116.1, C117.1, C118.1, C119.1, C120.1, C121.2, C122.1, C123.1, C124.2, C125.1, C126.1, C127.1, C128.2, C129.1, C130.1, C131.1, C132.1, C133.1, C134.1, C136.1, C137.1, C138.2, C139.1, C140.1, C141.1, C142.1, C143.1, C144.2, C145.1, C146.1, C147.2, C148.1, C149.2, C150.1, C151.2, C152.2, C153.1, C154.1, C155.1, C156.1, C157.1, C158.1, C159.1, C160.1, C161.1, C162.1, C163.1, C164.1, C165.1, C166.1, C167.1, C168.1, C169.2, C170.1, C171.2, C172.1, C173.2, C174.1, C175.2, C176.1, C177.1, C178.1, C179.1, C180.1, C181.1, C182.1, C183.2, C184.2, C185.2, C186.1, C187.2, C188.1, C189.1, C190.1, C191.1, C192.1, C193.1, C194.1, C195.1, C196.1, C197.2, C199.1, C200.1, C201.2, C202.2, C203.1, C204.1, C205.1, C206.1, C207.1, C208.1, C209.1, C210.1, C211.1, C212.1, C213.1, C214.1, C215.1, C216.1, C217.1, C218.2, C219.2, D1.2, DBG_UART1.3, GND1.1, GPIO1.2, GPIO_LED1.1, HSIC1.4, L7.2, LCD_CON1.0, LCD_CON1.2, LCD_CON1.4, LCD_CON1.5, LCD_CON1.6, LCD_CON1.13, LCD_CON1.14, LCD_CON1.21, LCD_CON1.22, LIPO_BAT1.2, MICRO_SD1.6, MICRO_SD1.10, MICRO_SD1.11, MICRO_SD1.12, MICRO_SD1.13, MIPI-DSI1.1, MIPI-DSI1.4, MIPI-DSI1.7, MIPI-DSI1.10, MIPI-DSI1.13, MIPI-DSI1.18, Mounting_hole1.0, Mounting_hole2.0, Mounting_hole3.0, PHYRST1.1, PWR1.-, PWRLED1.1, PWRON1.2, R7.1, R8.1, R9.2, R10.2, R12.1, R13.2, R14.2, R36.1, R40.1, R41.1, R42.1, R48.1, R49.1, R52.2, R55.2, R62.2, R81.2, R83.2, R84.1, R96.2, R97.2, R98.2, R107.2, R114.1, R115.2, R120.2, RESET1.2, U1.A1, U1.A23, U1.AC23, U1.C3, U1.C7, U1.D7, U1.G6, U1.G11, U1.H4, U1.H13, U1.J9, U1.J10, U1.J11, U1.J14, U1.J15, U1.K8, U1.K9, U1.K10, U1.K11, U1.K12, U1.K13, U1.L4, U1.L5, U1.L9, U1.L10, U1.L11, U1.L12, U1.L15, U1.M3, U1.M8, U1.M9, U1.M10, U1.M11, U1.M12, U1.M15, U1.N4, U1.N9, U1.N10, U1.N11, U1.N12, U1.N13, U1.N15, U1.P7, U1.P8, U1.P9, U1.P10, U1.P11, U1.P12, U1.P13, U1.R5, U1.R6, U1.R7, U1.R8, U1.R9, U1.R10, U1.R11, U1.R12, U1.R15, U1.T8, U1.T9, U1.T10, U1.T11, U1.T12, U1.T13, U1.U2, U1.U5, U1.U7, U1.U8, U1.U9, U1.U11, U1.U12, U1.V8, U1.V14, U2.A9, U2.B1, U2.B3, U2.B9, U2.D1, U2.D8, U2.E1, U2.E2, U2.E8, U2.F9, U2.G1, U2.G8, U2.G9, U2.J2, U2.J8, U2.M1, U2.M9, U2.P1, U2.P9, U2.T1, U2.T9, U3.A9, U3.B1, U3.B3, U3.B9, U3.D1, U3.D8, U3.E1, U3.E2, U3.E8, U3.F9, U3.G1, U3.G8, U3.G9, U3.J2, U3.J8, U3.M1, U3.M9, U3.P1, U3.P9, U3.T1, U3.T9, U4.4, U4.7, U5.A6, U5.C4, U5.E7, U5.G5, U5.H10, U5.J5, U5.K8, U5.N2, U5.N5, U5.P4, U5.P6, U6.2, U7.3, U7.8, U8.3, U8.8, U9.2, U10.3, U10.8, U11.1, U11.20, U11.31, U11.33, U11.36, U11.41, U12.4, U13.2, U14.12, U14.25, U14.45, U14.59, U14.69, U15.29, U15.49, UBOOT1.2, UEXT1.2, USB1.0, USB1.4, USB-OTG1.0, USB-OTG1.5, VR1.1, WP_Enable1.1
GNDA: C46.2, C47.1, C48.1, C49.2, C50.1, C51.2, C53.2, C54.1, C55.2, C56.1, C57.1, C59.2, C62.2, C63.2, C65.1, C66.1, GNDA1.1, MIC/LINEIN1.2, R27.2, R34.1, R35.1, R36.2, U1.A11
IPS: C126.2, C128.1, C133.2, C140.2, C141.2, C145.2, C147.1, C153.2, C157.2, C159.2, C167.2, C169.1, C176.2, CHGLED1.2, IPS1.1, L16.1, R131.1, T1.4, T1.8, U13.5, U14.4, U14.6, U14.11, U14.15, U14.19, U14.22, U14.32, U14.38, U14.39, U14.40, U14.55, U14.56, U14.66, U14.67
KEYADC: C193.2, GPIO1.8, R103.2, U1.A16
unnamed: 3.3V/VCC-PE:2.8V1.2, C194.2, R101.2, R102.2, U1.U18
unnamed: ANT1.1, R16.1
unnamed: ANT2.1, R17.1
unnamed: C37.2, C38.2, U5.C2
unnamed: C42.1, C43.1, C44.1, L1.2, U5.E6, U5.F5, U5.J10, U5.K9
unnamed: C45.1, LINEINR/MICIN1.3
unnamed: C48.2, C82.1, C84.2
unnamed: C51.1, C53.1, U1.C11
unnamed: C52.1, C84.1, LINEINR/MICIN1.1, R29.1
unnamed: C54.2, C56.2, U1.F12, U1.G13
unnamed: C55.1, U1.B12
unnamed: C57.2, R25.1, R26.2, R29.2
unnamed: C58.1, LINEINL/MICIN2.3
unnamed: C59.1, R27.1, U1.B11
unnamed: C60.1, C85.1, LINEINL/MICIN2.1, R26.1
unnamed: C61.1, U1.E11
unnamed: C61.2, U1.E10
unnamed: C62.1, C83.1, C85.2
unnamed: C63.1, U1.D13
unnamed: C64.1, L2.2, MICRO_SD1.4
unnamed: C65.2, R63.1
unnamed: C66.2, R64.1
unnamed: C68.2, C69.2, C70.2, L6.1, R38.2, U6.1
unnamed: C74.1, L8.2, USB1.1
unnamed: C75.2, C76.2, C77.2, L8.1, U9.1
unnamed: C86.2, HPHONEOUTR/LINEOUTR1.3
unnamed: C87.2, HPHONEOUTL/LINEOUTL1.3
unnamed: C88.2, L9.1
unnamed: C105.1, U11.2
unnamed: C105.2, C106.2, L10.2
unnamed: C107.2, L10.1, R16.2, R17.2
unnamed: C125.2, U14.18
unnamed: C135.1, C138.1, C144.1, L18.1, R78.1, T1.1, T1.2, T1.5, T1.6, T1.7, U14.63
unnamed: C143.2, D2.1, FET2.2, R80.1
unnamed: C149.1, U14.35
unnamed: C151.1, U14.34
unnamed: C174.2, U14.2
unnamed: C177.2, R28.2, R91.2, U14.60
unnamed: C181.2, R92.2, U14.50
unnamed: C182.2, U14.33
unnamed: C183.1, Q2.1, R93.1, U1.B19
unnamed: C184.1, Q2.2, R93.2, U1.C18
unnamed: C185.1, Q3.1, R94.2
unnamed: C187.1, Q3.2, U1.K22
unnamed: C188.2, U1.P16
unnamed: C192.2, U1.G16
unnamed: C198.2, L7.1
unnamed: C204.2, C205.2, C206.2, C208.2, C209.2, C210.2, L24.1, U15.14, U15.18, U15.23, U15.26, U15.30, U15.39
unnamed: C207.2, C214.2, C215.2, L23.1, U15.4, U15.9, U15.44
unnamed: C211.2, PHYRST1.2, R116.1, R117.1, R118.1, U15.42
unnamed: C212.2, Q4.1, U15.46
unnamed: C213.2, Q4.2, U15.45
unnamed: C218.1, D5.1, VR1.3
unnamed: CHGLED1.1, R82.2
unnamed: D2.2, L16.2, U13.1
unnamed: D4.1, DBG_UART1.2
unnamed: D4.2, R95.1, U1.Y7
unnamed: DBG_UART1.1, U1.V10
unnamed: GPIO_LED1.2, R58.2
unnamed: HEADPHONES/LINEOUT1.1, L5.2
unnamed: HEADPHONES/LINEOUT1.2, L4.2
unnamed: HEADPHONES/LINEOUT1.3, L3.2
unnamed: HEADPHONES/LINEOUT1.4, R32.1, R59.1
unnamed: HPHONEOUTL/LINEOUTL1.2, L5.1
unnamed: HPHONEOUTR/LINEOUTR1.2, L3.1
unnamed: HSIC1.1, HSIC_E1.2
unnamed: HSIC1.2, U1.H19
unnamed: HSIC1.3, U1.G19
unnamed: L14.1, U14.21
unnamed: L15.1, U14.43, U14.44
unnamed: L17.1, U14.36, U14.37
unnamed: L18.2, U14.65
unnamed: L19.1, U14.7
unnamed: L20.1, U14.10
unnamed: LINEINL/MICIN2.2, MIC/LINEIN1.1
unnamed: LINEINR/MICIN1.2, MIC/LINEIN1.3
unnamed: MICRO_SD1.5, R33.1
unnamed: MIPI-DSI1.16, R129.2, R131.2
unnamed: MIPI-DSI1.17, R125.1, R127.1
unnamed: MIPI-DSI1.19, R126.1, R128.1
unnamed: MIPI-DSI1.20, R130.2, R132.2
unnamed: PWRLED1.2, R74.2
unnamed: PWRON1.1, R91.1
unnamed: R3.2, U1.G2
unnamed: R4.2, U1.G3
unnamed: R7.2, U1.U1
unnamed: R9.1, U2.L8
unnamed: R10.1, U3.L8
unnamed: R13.1, U2.L9
unnamed: R14.1, U3.L9
unnamed: R15.1, U5.H5
unnamed: R19.1, U1.AB12
unnamed: R41.2, U6.3
unnamed: R49.2, U9.3
unnamed: R54.1, U11.17
unnamed: R55.1, R56.1, U12.3, WP_Enable1.2
unnamed: R57.1, U12.7
unnamed: R60.1, U11.24
unnamed: R72.1, U1.AB11
unnamed: R80.2, R81.1, U13.3
unnamed: R82.1, U14.53
unnamed: R83.1, U14.30
unnamed: R86.1, U14.26
unnamed: R87.1, U14.27
unnamed: R89.1, RESET1.1
unnamed: R94.1, U1.K23
unnamed: R96.1, U1.H14
unnamed: R97.1, U1.AA11
unnamed: R98.1, U1.AA12
unnamed: R105.2, R106.2, U15.33
unnamed: R18.2, R107.1, U15.35
unnamed: R109.2, R110.2, U15.41
unnamed: R111.2, R112.2, U15.17
unnamed: R113.2, R114.2, U15.15
unnamed: R115.1, U15.48
unnamed: R119.1, U15.38
unnamed: RM1.1.2, U1.AC13
unnamed: RM1.2.2, U1.AB13
unnamed: RM1.3.2, U1.AC14
unnamed: RM1.4.2, U1.AB14
unnamed: RM8.1.2, RM15.1.1, U15.32
unnamed: RM8.2.2, RM15.2.1, U15.31
unnamed: RM8.3.2, RM15.3.1, U15.28
unnamed: RM8.4.2, RM15.4.1, U15.27
unnamed: T1.3, U14.52
PC4: GPIO1.20, U1.T20
PC7: GPIO1.22, U1.T19
PH10: LCD_CON1.33, R73.1, U1.Y8
PH11: LCD_CON1.34, U1.AA5
PL7: GPIO1.24, U1.C19
PL8: GPIO1.26, U1.B21
PL9: GPIO1.28, U1.D20
PL10: GPIO1.30, U1.D21
PL11: GPIO1.32, U1.C20
PL12: GPIO1.34, U1.D22
PMU-SCK: R88.1, U1.D17, U14.47
PMU-SDA: R90.1, U1.C17, U14.48
SPI0_CLK: R122.2, U1.P20, U12.6
SPI0_CS: R53.1, R124.1, U1.P19, U12.1
SPI0_MISO: R66.1, R121.2, U12.2
SPI0_MOSI: R123.1, U1.T21, U12.5
TWI0-SCK: LCD_CON1.39, MIPI-DSI1.11, R70.1, U1.W11
TWI0-SDA: LCD_CON1.40, MIPI-DSI1.12, R71.1, U1.AA10
TWI1-SCK: R75.2, U1.AC4, U4.6, UEXT1.5
TWI1-SDA: R77.2, U1.AA9, U4.5, UEXT1.6
UART3-RX: R76.2, U1.AC7, UEXT1.4
UART3-TX: U1.AB5, UEXT1.3
UBOOT: GPIO1.6, U1.F17, UBOOT1.1
USB0-DRV: R40.2, U6.4, U14.51
USB0-D_N: R87.2, U1.B22, USB-OTG1.2
USB0-D_P: R86.2, U1.A22, USB-OTG1.3
USB1-DRV: R48.2, R99.2, U1.U21, U9.4
VBAT: C135.2, C180.2, LIPO_BAT1.1, R78.2, U14.64
VCC-PC: C34.2, C35.2, C36.2, PWR_PC1.2, R21.2, R23.2, R67.2, U1.R16, U5.C6, U5.M4, U5.N4, U5.P3, U5.P5, VCC-PC1.1
VCC-PE: 3.3V/VCC-PE:2.8V1.1, C171.1, GPIO1.40, U14.28
VCC-PL: C109.1, C173.1, R88.2, R90.2, U1.J16, U14.29, VCC-PL1.1
VDDFB-CPUX: U1.T6, U14.41, U14.42

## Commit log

2021-11-11 patent images
2021-11-11 Added documents
2021-11-11 patent added
2021-11-11 added specifications of components
2021-11-12 debug application
2021-11-12 Added android and linux images
2021-11-17 Hardware files prepared
2021-11-18 added patent in russian

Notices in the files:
hardware/Crystal-HUD v2.3.kicad_pcb:
(c) 2020
